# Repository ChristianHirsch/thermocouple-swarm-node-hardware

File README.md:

# wort-swarm-node-hardware

This piece of hardware is used to read temperature using a K-type thermocouple. It consists of a Noric nRF52840 system on chip (SoC), a MAX31855K thermocouple to digital converter and battery management.

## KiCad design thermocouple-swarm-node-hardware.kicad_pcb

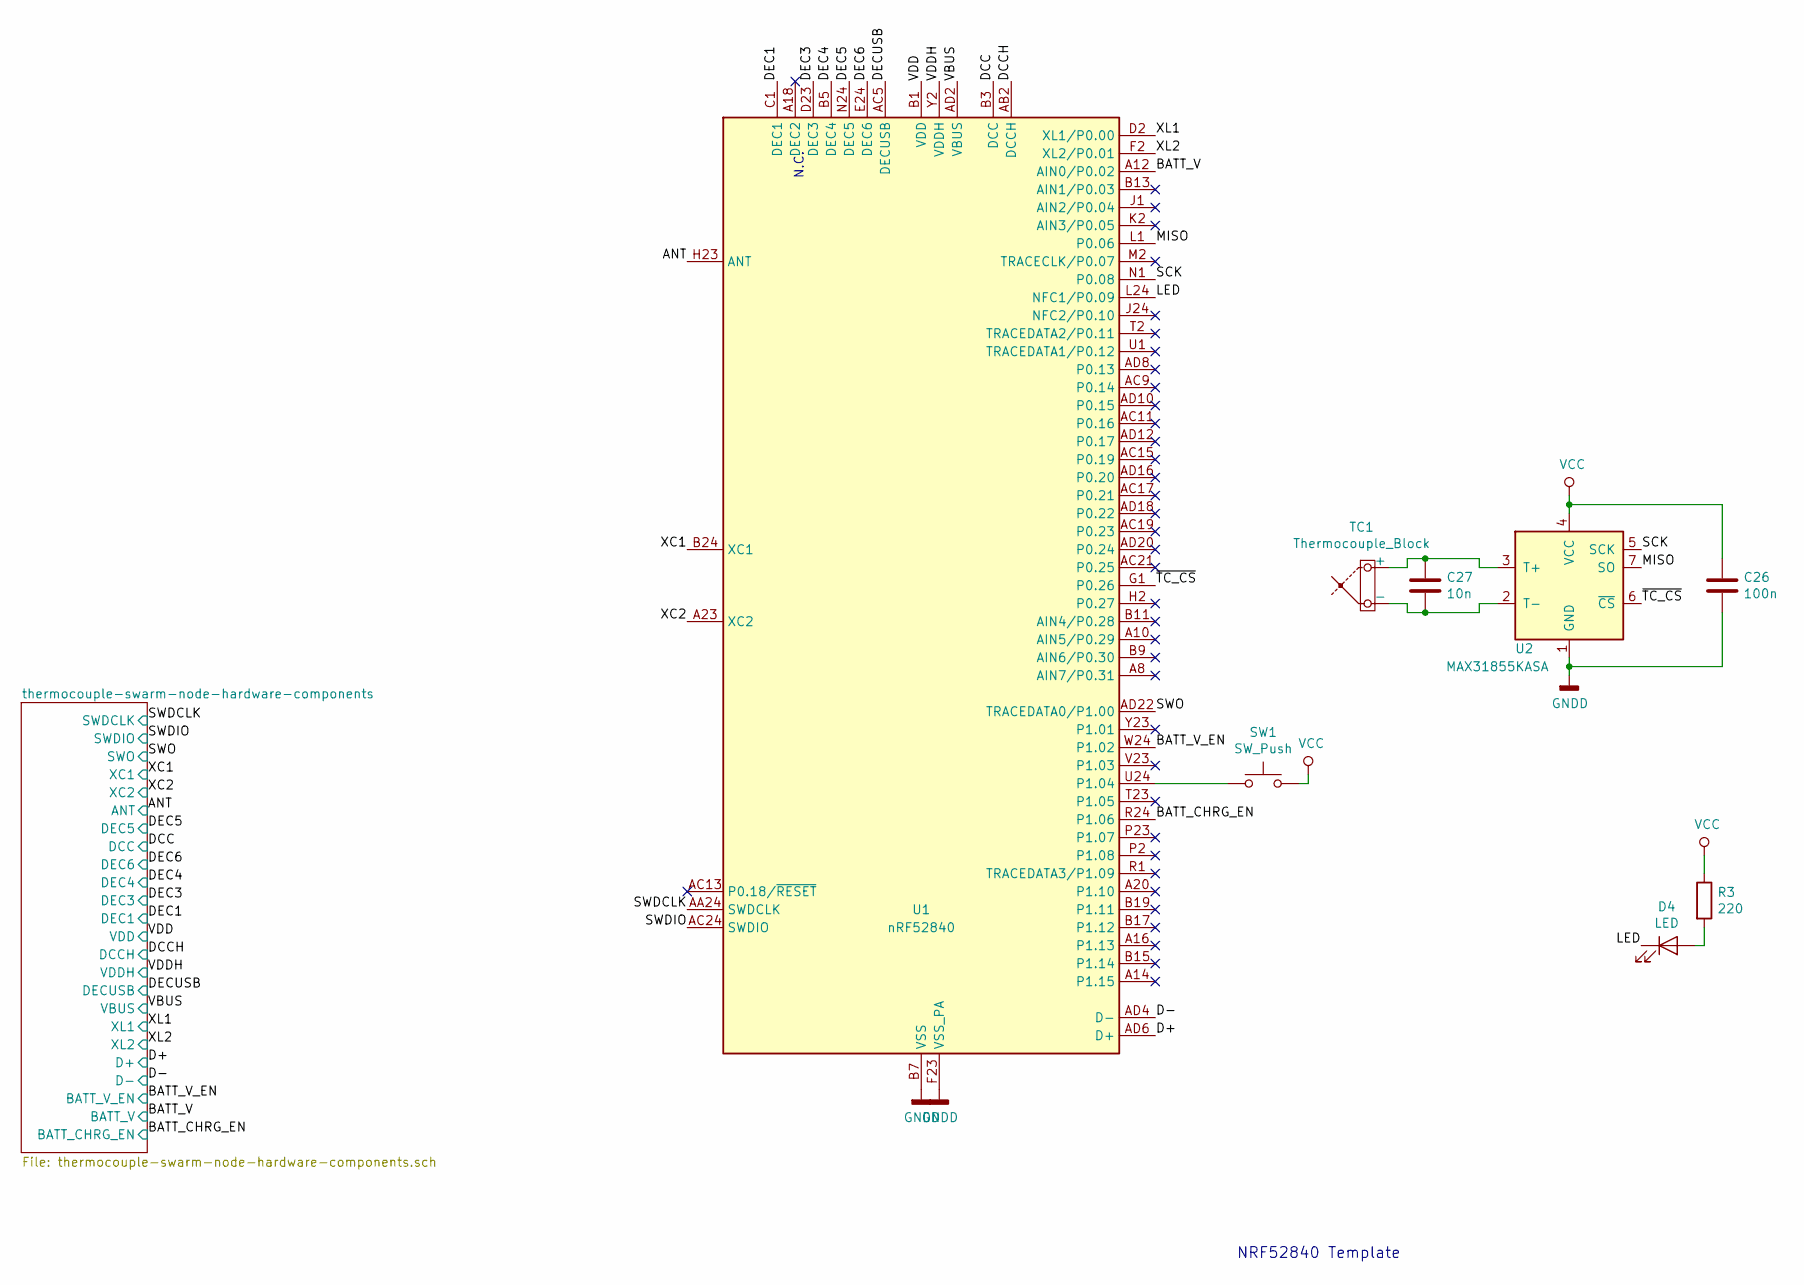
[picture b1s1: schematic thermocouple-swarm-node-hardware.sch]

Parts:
C26: 100n; C_0402_1005Metric
C27: 10n; C_0402_1005Metric
D4: LED; LED_0603_1608Metric
R3: 220; R_0402_1005Metric
SW1: SW_Push; SW_SPST_B3U-3000P
TC1: Thermocouple_Block; TerminalBlock_bornier-2_P5.08mm
U1: nRF52840; Nordic_AQFN-73-1EP_7x7mm_P0.5mm
U2: MAX31855KASA; SOIC-8_3.9x4.9mm_P1.27mm

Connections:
/ANT: U1.H23 (ANT); also elsewhere on the board
/BATT_CHRG_EN: U1.R24 (P1.06); also elsewhere on the board
/BATT_V: U1.A12 (AIN0/P0.02); also elsewhere on the board
/BATT_V_EN: U1.W24 (P1.02); also elsewhere on the board
/D+: U1.AD6 (D+); also elsewhere on the board
/D-: U1.AD4 (D-); also elsewhere on the board
/DCC: U1.B3 (DCC); also elsewhere on the board
/DCCH: U1.AB2 (DCCH); also elsewhere on the board
/DEC1: U1.C1 (DEC1); also elsewhere on the board
/DEC3: U1.D23 (DEC3); also elsewhere on the board
/DEC4: U1.B5 (DEC4), U1.E24 (DEC6); also elsewhere on the board
/DEC5: U1.N24 (DEC5); also elsewhere on the board
/DECUSB: U1.AC5 (DECUSB); also elsewhere on the board
/LED: D4.1 (K), U1.L24 (NFC1/P0.09)
/MISO: U1.L1 (P0.06), U2.7 (SO)
/SCK: U1.N1 (P0.08), U2.5 (SCK)
/SWDCLK: U1.AA24 (SWDCLK); also elsewhere on the board
/SWDIO: U1.AC24 (SWDIO); also elsewhere on the board
/SWO: U1.AD22 (TRACEDATA0/P1.00); also elsewhere on the board
/XC1: U1.B24 (XC1); also elsewhere on the board
/XC2: U1.A23 (XC2); also elsewhere on the board
/XL1: U1.D2 (XL1/P0.00); also elsewhere on the board
/XL2: U1.F2 (XL2/P0.01); also elsewhere on the board
/~TC_CS: U1.G1 (P0.26), U2.6 (~CS~)
GND: C26.2, U1.B7 (VSS), U1.EP (VSS), U1.F23 (VSS_PA), U2.1 (GND); also elsewhere on the board
LINE: U1.Y2 (VDDH); also elsewhere on the board
unnamed: C27.1, TC1.1 (+), U2.3 (T+)
unnamed: C27.2, TC1.2 (-), U2.2 (T-)
unnamed: D4.2 (A), R3.2
unnamed: SW1.1, U1.U24 (P1.04)
VBUS: U1.AD2 (VBUS); also elsewhere on the board
VCC: C26.1, R3.1, SW1.2, U1.A22 (VDD), U1.AD14 (VDD), U1.AD23 (VDD), U1.B1 (VDD), U1.W1 (VDD), U2.4 (VCC); also elsewhere on the board

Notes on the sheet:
NRF52840 Template
N.C.

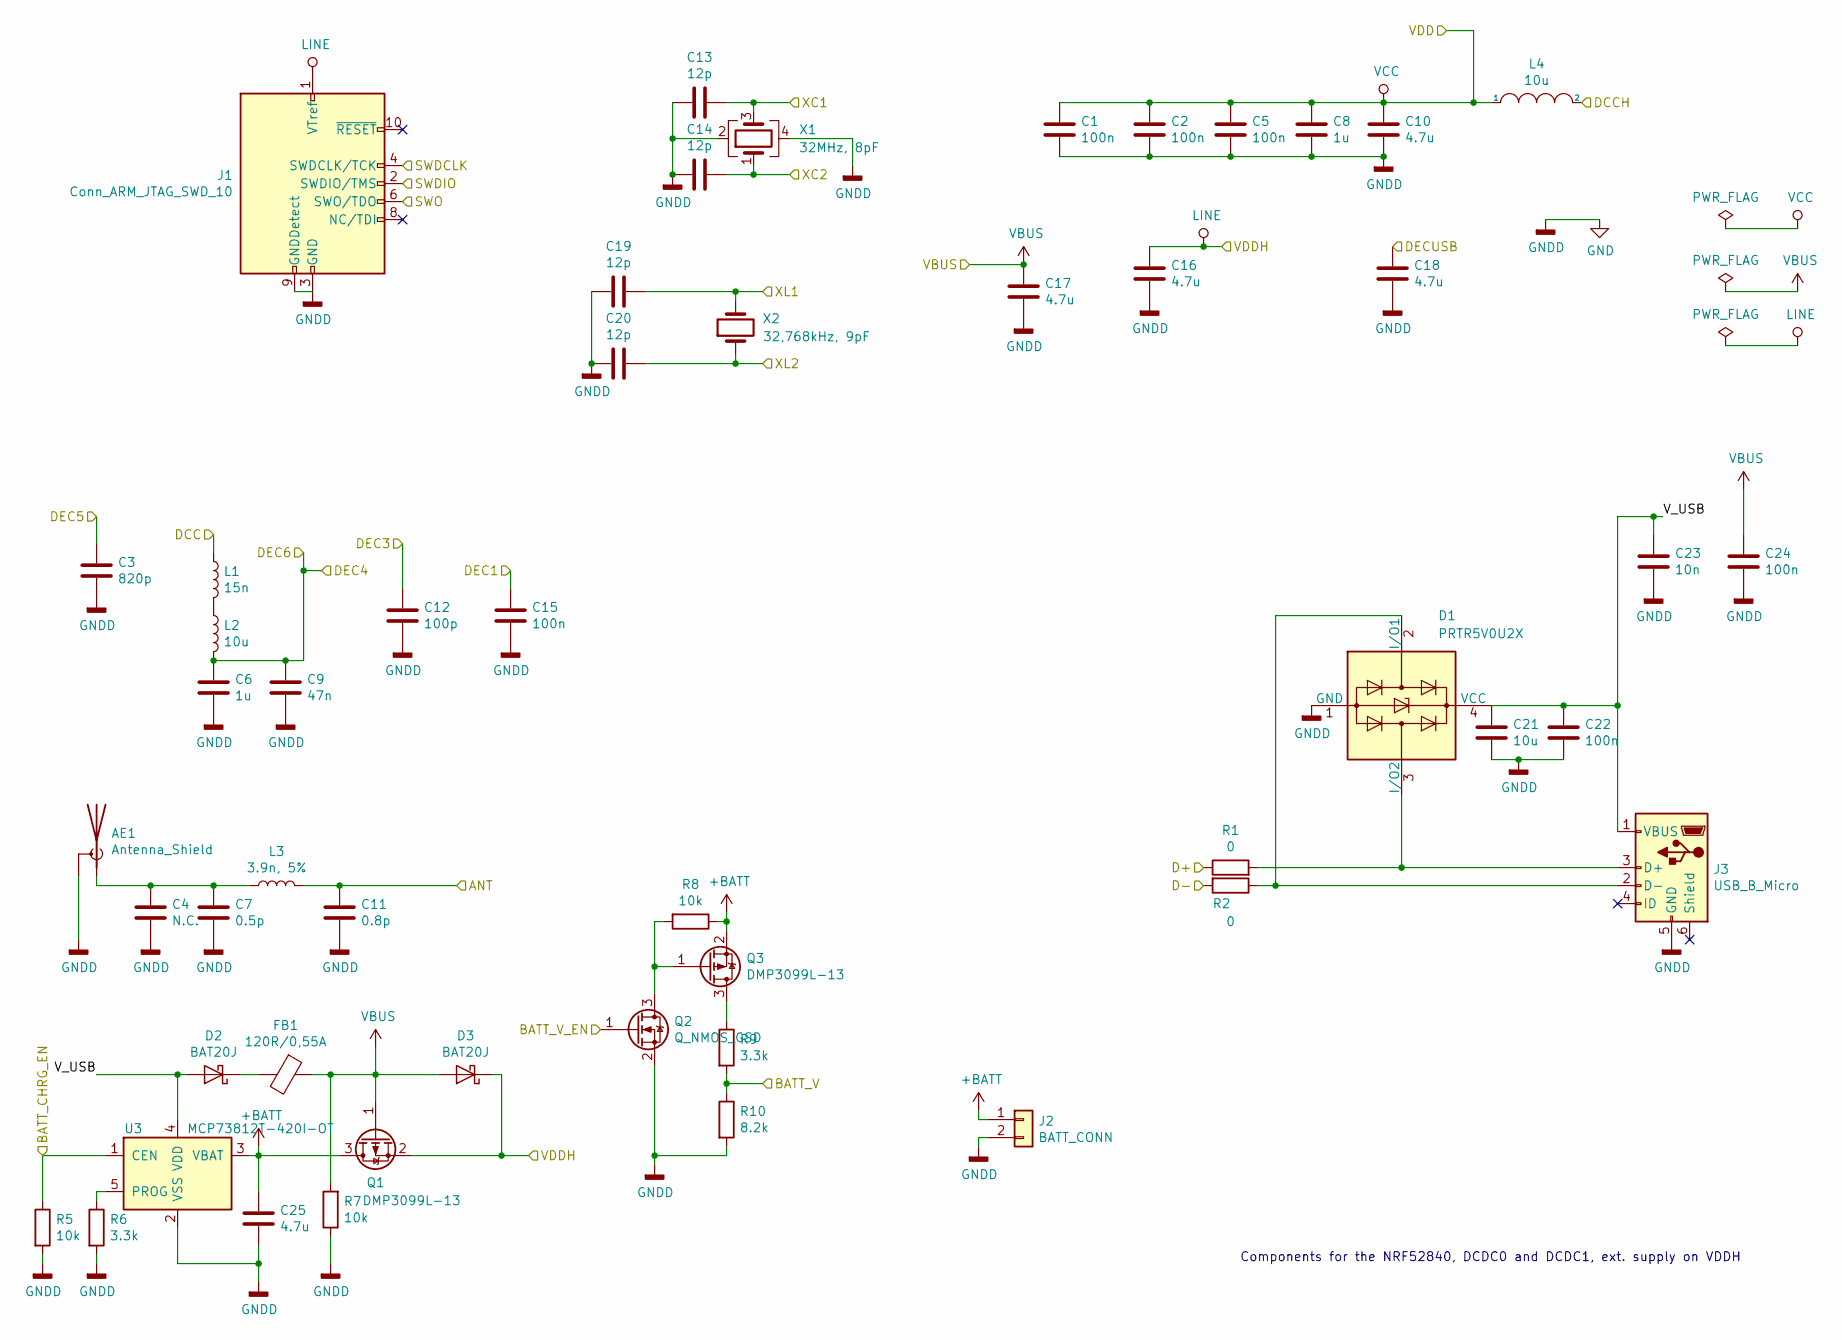
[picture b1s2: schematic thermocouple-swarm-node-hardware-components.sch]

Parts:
AE1: Antenna_Shield; Texas_SWRA117D_2.4GHz_Right
C1, C2, C5, C15, C22, C24: 100n; C_0402_1005Metric
C3: 820p; C_0402_1005Metric
C4: N.C.; C_0402_1005Metric
C6, C8: 1u; C_0603_1608Metric
C7: 0.5p; C_0402_1005Metric
C9: 47n; C_0402_1005Metric
C10, C16, C17, C18, C25: 4.7u; C_0603_1608Metric
C11: 0.8p; C_0402_1005Metric
C12: 100p; C_0402_1005Metric
C13, C14, C19, C20: 12p; C_0402_1005Metric
C21: 10u; C_0603_1608Metric
C23: 10n; C_0402_1005Metric
D1: PRTR5V0U2X; SOT-143
D2, D3: BAT20J; D_SOD-323
FB1: 120R/0,55A; L_0402_1005Metric
J1: Conn_ARM_JTAG_SWD_10; PinHeader_2x05_P1.27mm_Vertical_SMD
J2: BATT_CONN; BatteryHolder_Keystone_1042_1x18650
J3: USB_B_Micro; USB_Micro-B_Molex_47346-0001
L1: 15n; L_0402_1005Metric
L2, L4: 10u; L_0603_1608Metric
L3: 3.9n, 5%; L_0402_1005Metric
Q1, Q3: DMP3099L-13; SOT-23
Q2: Q_NMOS_GSD; SOT-23
R1, R2: 0; R_0402_1005Metric
R5, R7, R8: 10k; R_0402_1005Metric
R6, R9: 3.3k; R_0402_1005Metric
R10: 8.2k; R_0402_1005Metric
U3: MCP73812T-420I-OT; SOT-23-5
X1: 32MHz, 8pF; Crystal_SMD_2016-4Pin_2.0x1.6mm
X2: 32,768kHz, 9pF; Crystal_SMD_3215-2Pin_3.2x1.5mm

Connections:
+BATT: C25.1, J2.1, Q1.3 (D), Q3.2 (S), R8.1, U3.3 (VBAT)
/ANT: C11.1, L3.2; also elsewhere on the board
/BATT_CHRG_EN: R5.1, U3.1 (CEN); also elsewhere on the board
/BATT_V: R9.2, R10.1; also elsewhere on the board
/BATT_V_EN: Q2.1 (G); also elsewhere on the board
/D+: R1.1; also elsewhere on the board
/D-: R2.2; also elsewhere on the board
/DCC: L1.1; also elsewhere on the board
/DCCH: L4.2; also elsewhere on the board
/DEC1: C15.1; also elsewhere on the board
/DEC3: C12.1; also elsewhere on the board
/DEC4: C6.1, C9.1, L2.2; also elsewhere on the board
/DEC5: C3.1; also elsewhere on the board
/DECUSB: C18.1; also elsewhere on the board
/SWDCLK: J1.4 (SWDCLK/TCK); also elsewhere on the board
/SWDIO: J1.2 (SWDIO/TMS); also elsewhere on the board
/SWO: J1.6 (SWO/TDO); also elsewhere on the board
/XC1: C13.2, X1.3; also elsewhere on the board
/XC2: C14.2, X1.1; also elsewhere on the board
/XL1: C19.2, X2.2; also elsewhere on the board
/XL2: C20.2, X2.1; also elsewhere on the board
/thermocouple-swarm-node-hardware-components/V_USB: C21.1, C22.1, C23.1, D1.4 (VCC), D2.2 (A), J3.1 (VBUS), U3.4 (VDD)
GND: AE1.2 (Shield), C1.2, C2.2, C3.2, C4.2, C5.2, C6.2, C7.2, C8.2, C9.2, C10.2, C11.2, C12.2, C13.1, C14.1, C15.2, C16.2, C17.2, C18.2, C19.1, C20.1, C21.2, C22.2, C23.2, C24.2, C25.2, D1.1 (GND), J1.3 (GND), J1.5 (GND), J1.9 (GNDDetect), J2.2, J3.5 (GND), Q2.2 (S), R5.2, R6.2, R7.1, R10.2, U3.2 (VSS), X1.2, X1.4; also elsewhere on the board
LINE: C16.1, D3.1 (K), J1.1 (VTref), Q1.2 (S); also elsewhere on the board
unnamed: AE1.1 (A), C4.1, C7.1, L3.1
unnamed: D1.2 (I/O1), J3.2 (D-), R2.1
unnamed: D1.3 (I/O2), J3.3 (D+), R1.2
unnamed: D2.1 (K), FB1.2
unnamed: L1.2, L2.1
unnamed: Q2.3 (D), Q3.1 (G), R8.2
unnamed: Q3.3 (D), R9.1
unnamed: R6.1, U3.5 (PROG)
VBUS: C17.1, C24.1, D3.2 (A), FB1.1, Q1.1 (G), R7.2; also elsewhere on the board
VCC: C1.1, C2.1, C5.1, C8.1, C10.1, L4.1; also elsewhere on the board

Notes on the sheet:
Components for the NRF52840, DCDC0 and DCDC1, ext. supply on VDDH

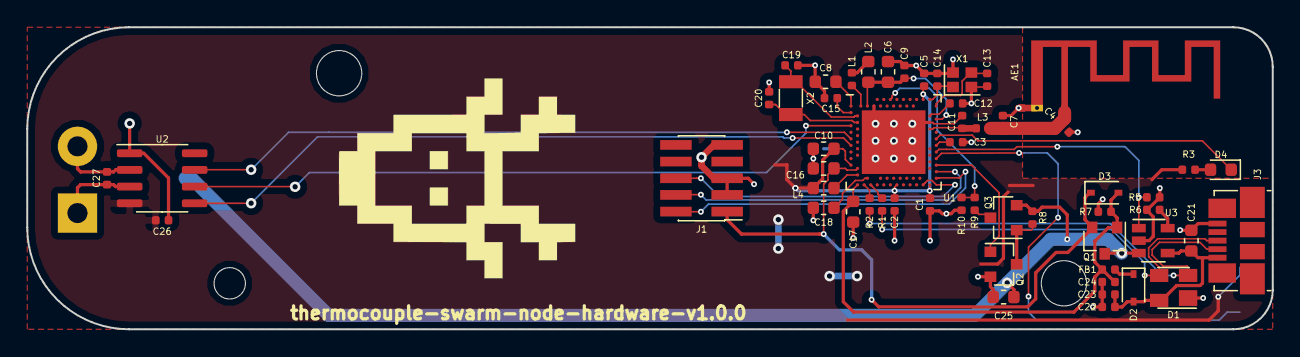
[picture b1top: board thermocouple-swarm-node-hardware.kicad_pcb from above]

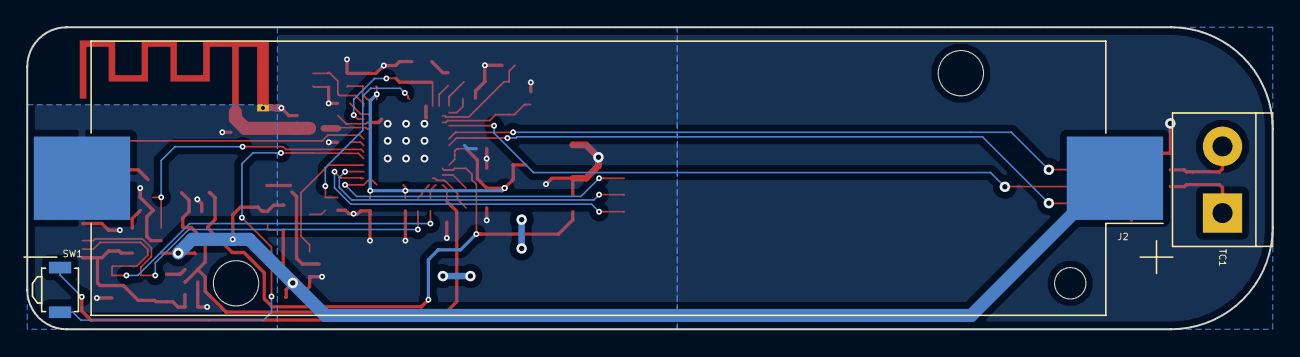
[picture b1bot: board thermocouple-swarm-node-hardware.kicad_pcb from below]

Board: 2 copper layers, 94.9 x 23.0 mm, 59 parts (3 on the bottom side), 42 nets.
